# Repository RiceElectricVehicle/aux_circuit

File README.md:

View this project on [CADLAB.io](https://cadlab.io/project/1338). 

# aux_circuit

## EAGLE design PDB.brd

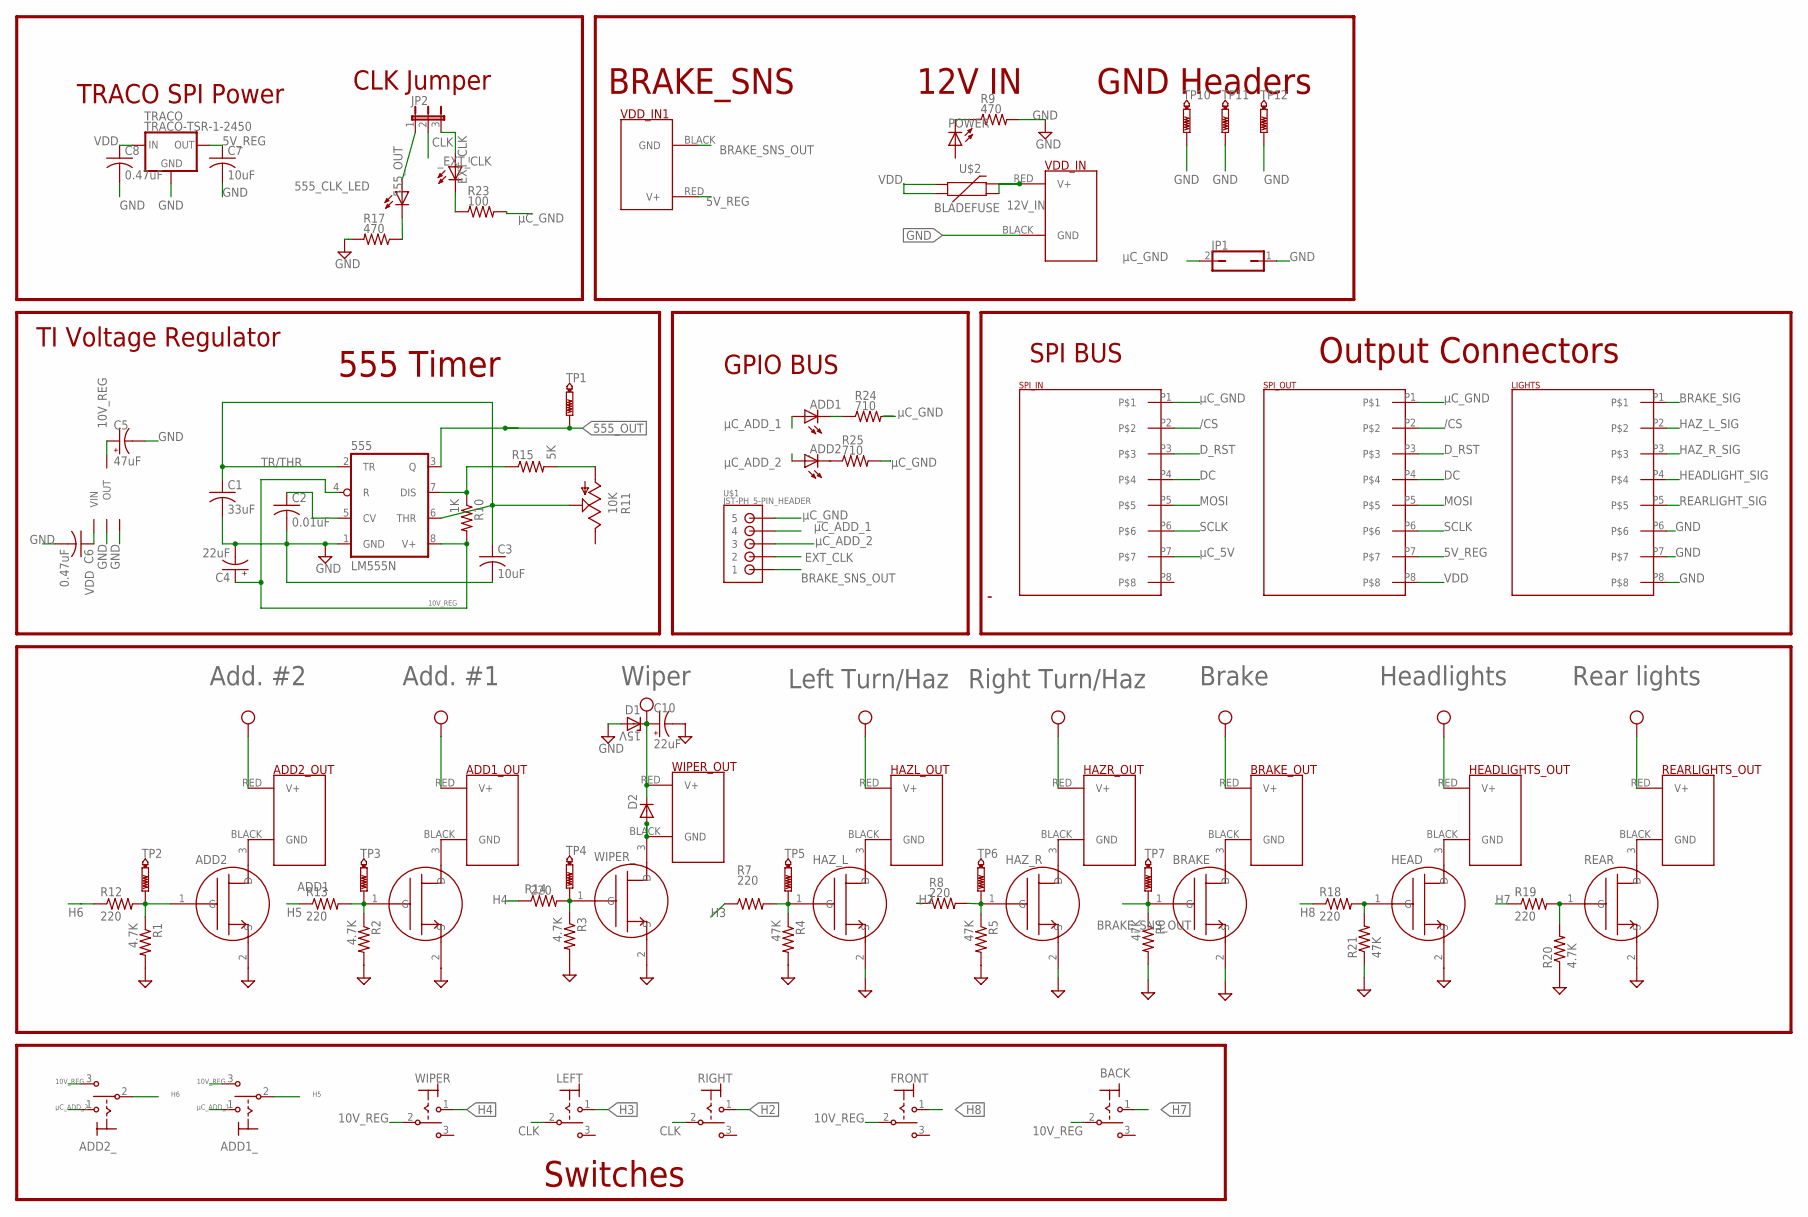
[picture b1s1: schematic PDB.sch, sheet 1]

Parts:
555: LM555N; DIL08
555_CLK_LED: LEDCHIPLED_0805; CHIPLED_0805
ADD1, ADD2: NCV8405ADPAK-3PIN; TO254P1054X240-3
ADD1_, ADD2_: M9040P
ADD1_OUT, ADD2_OUT: POWERPOLE_POWER25A_HORIZONTAL_G2; POWERPOLE_PAIR_25A_HORIZ_G2
BACK: M9040P
BRAKE: NCV8405ADPAK-3PIN; TO254P1054X240-3
BRAKE_OUT: POWERPOLE_POWER25A_HORIZONTAL_G2; POWERPOLE_PAIR_25A_HORIZ_G2
C1: 33uF; C0805
C2: 0.01uF; C0805
C3, C7: 10uF; C0805
C4, C10: 22uF; PANASONIC_C
C5: 47uF; PANASONIC_C
C6, C8: 0.47uF; C0805
D1: 15V; DO41Z10
D2: 1N4446; DO35-10
FRONT: M9040P
HAZL_OUT: POWERPOLE_POWER25A_HORIZONTAL_G2; POWERPOLE_PAIR_25A_HORIZ_G2
HAZR_OUT: POWERPOLE_POWER25A_HORIZONTAL_G2; POWERPOLE_PAIR_25A_HORIZ_G2
HAZ_L: NCV8405ADPAK-3PIN; TO254P1054X240-3
HAZ_R: NCV8405ADPAK-3PIN; TO254P1054X240-3
HEAD: NCV8405ADPAK-3PIN; TO254P1054X240-3
HEADLIGHTS_OUT: POWERPOLE_POWER25A_HORIZONTAL_G2; POWERPOLE_PAIR_25A_HORIZ_G2
JP1: JP1Q; JP1
JP2: JP2E; JP2
LEFT: M9040P
LIGHTS: 8-PIN-MOLEX-RA-FEMALE; 8-PIN-MOLEX
LM2940: LM2940LM; SOT230P700X180-4
POWER: LEDCHIPLED_0805; CHIPLED_0805
R1, R2, R3, R20: 4.7K; R0805
R4, R5, R6, R21: 47K; R0805
R7, R8, R12, R13, R14, R18, R19: 220; R0805
R9, R17: 470; R3225
R10: 1K; R0805
R11: 10K; B25U
R15: 5K; R0805
R23: 100; R0805
R24, R25: 710; R0805
REAR: NCV8405ADPAK-3PIN; TO254P1054X240-3
REARLIGHTS_OUT: POWERPOLE_POWER25A_HORIZONTAL_G2; POWERPOLE_PAIR_25A_HORIZ_G2
RIGHT: M9040P
SPI_IN: 8-PIN-MOLEX-RA-FEMALE; 8-PIN-MOLEX
SPI_OUT: 8-PIN-MOLEX-RA-FEMALE; 8-PIN-MOLEX
TP1, TP2, TP3, TP4, TP5, TP6, TP7: PTR1B2,54; B2,54
TP10, TP11, TP12: PTR1PAD1-13Y; P1-13Y
TRACO: TRACO-TSR-1-2450; SIP3
U$1: JST-PH_5-PIN_HEADER; JST_B5B-PH_HEADER
U$2: BLADEFUSE
VDD_IN, VDD_IN1: POWERPOLE_POWER25A_HORIZONTAL_G2; POWERPOLE_PAIR_25A_HORIZ_G2
WIPER: M9040P
WIPER_: NCV8405ADPAK-3PIN; TO254P1054X240-3
WIPER_OUT: POWERPOLE_POWER25A_HORIZONTAL_G2; POWERPOLE_PAIR_25A_HORIZ_G2
_ADD1, _ADD2: LEDCHIPLED_0805; CHIPLED_0805
_EXT_CLK: LEDCHIPLED_0805; CHIPLED_0805

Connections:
5V_REG: C7.1, SPI_OUT.P7, TRACO.3 (OUT), VDD_IN1.RED (V+)
10V_REG: 555.4 (R), 555.8 (V+), ADD1_.3 (S), ADD2_.3 (S), BACK.2, C4.+, C5.+, FRONT.2, LM2940.3 (OUT), R10.2, WIPER.2
12V_IN: U$2.P$3 (2), U$2.P$4, VDD_IN.RED (V+)
555_OUT: 555.3 (Q), 555_CLK_LED.A, JP2.1, TP1.TP
/CS: SPI_IN.P2, SPI_OUT.P2
BRAKE_SIG: BRAKE.3 (D), BRAKE_OUT.BLACK (GND), LIGHTS.P1
BRAKE_SNS_OUT: BRAKE.1 (G), R6.1, TP7.TP, U$1.P1 (1), VDD_IN1.BLACK (GND)
CLK: JP2.2, LEFT.2, RIGHT.2
CV: 555.5 (CV), C2.1
DC: SPI_IN.P4, SPI_OUT.P4
DIS: 555.7 (DIS), R10.1, R15.1
D_RST: SPI_IN.P3, SPI_OUT.P3
EXT_CLK: JP2.3, U$1.P2 (2), _EXT_CLK.A
GND: 555.1 (GND), ADD1.2 (S), ADD2.2 (S), BRAKE.2 (S), C1.2, C2.2, C3.2, C4.-, C5.-, C6.2, C7.2, C8.2, C10.-, D1.A, HAZ_L.2 (S), HAZ_R.2 (S), HEAD.2 (S), JP1.1, LIGHTS.P6, LIGHTS.P7, LIGHTS.P8, LM2940.2 (GND2), LM2940.4 (GND), R1.2, R2.2, R3.2, R4.2, R5.2, R6.2, R9.2, R17.2, R20.1, R21.1, REAR.2 (S), TP10.TP, TP11.TP, TP12.TP, TRACO.2 (GND), VDD_IN.BLACK (GND), WIPER_.2 (S)
H2: R8.1, RIGHT.1 (O)
H3: LEFT.1 (O), R7.1
H4: R14.1, WIPER.1 (O)
H5: ADD1_.2, R13.1
H6: ADD2_.2, R12.1
H7: BACK.1 (O), R19.1
H8: FRONT.1 (O), R18.1
HAZ_L_SIG: HAZL_OUT.BLACK (GND), HAZ_L.3 (D), LIGHTS.P2
HAZ_R_SIG: HAZR_OUT.BLACK (GND), HAZ_R.3 (D), LIGHTS.P3
HEADLIGHT_SIG: HEAD.3 (D), HEADLIGHTS_OUT.BLACK (GND), LIGHTS.P4
HL_GATE: HAZ_L.1 (G), R4.1, R7.2, TP5.TP
HR_GATE: HAZ_R.1 (G), R5.1, R8.2, TP6.TP
MOSI: SPI_IN.P5, SPI_OUT.P5
unnamed: POWER.C, R9.1
unnamed: 555_CLK_LED.C, R17.1
unnamed: R23.1, _EXT_CLK.C
unnamed: R24.1, _ADD1.C
unnamed: R25.1, _ADD2.C
unnamed: R11.A, R15.2
unnamed: ADD2.1 (G), R1.1, R12.2, TP2.TP
unnamed: ADD2.3 (D), ADD2_OUT.BLACK (GND)
unnamed: HEAD.1 (G), R18.2, R21.2
unnamed: R19.2, R20.2, REAR.1 (G)
unnamed: ADD1.3 (D), ADD1_OUT.BLACK (GND)
unnamed: D2.A, WIPER_.3 (D), WIPER_OUT.BLACK (GND)
unnamed: R3.1, R14.2, TP4.TP, WIPER_.1 (G)
unnamed: ADD1.1 (G), R2.1, R13.2, TP3.TP
REARLIGHT_SIG: LIGHTS.P5, REAR.3 (D), REARLIGHTS_OUT.BLACK (GND)
SCLK: SPI_IN.P6, SPI_OUT.P6
TR/THR: 555.2 (TR), 555.6 (THR), C1.1, C3.1, R11.S
VDD: ADD1_OUT.RED (V+), ADD2_OUT.RED (V+), BRAKE_OUT.RED (V+), C6.1, C8.1, C10.+, D1.C, D2.C, HAZL_OUT.RED (V+), HAZR_OUT.RED (V+), HEADLIGHTS_OUT.RED (V+), LM2940.1 (VIN), REARLIGHTS_OUT.RED (V+), SPI_OUT.P8, TRACO.1 (IN), U$2.P$1 (1), U$2.P$2, WIPER_OUT.RED (V+)
µC_5V: SPI_IN.P7
µC_ADD_1: ADD1_.1 (O), U$1.P4 (4), _ADD1.A
µC_ADD_2: ADD2_.1 (O), U$1.P3 (3), _ADD2.A
µC_GND: JP1.2, R23.2, R24.2, R25.2, SPI_IN.P1, SPI_OUT.P1, U$1.P5 (5)

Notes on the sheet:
555 Timer
12V IN
BRAKE_SNS
Switches
Add. #2
Add. #1
Wiper
Left Turn/Haz
Right Turn/Haz
Brake
Headlights
Rear lights
GND Headers
Output Connectors
GPIO BUS
TRACO SPI Power
TI Voltage Regulator
CLK Jumper
SPI BUS

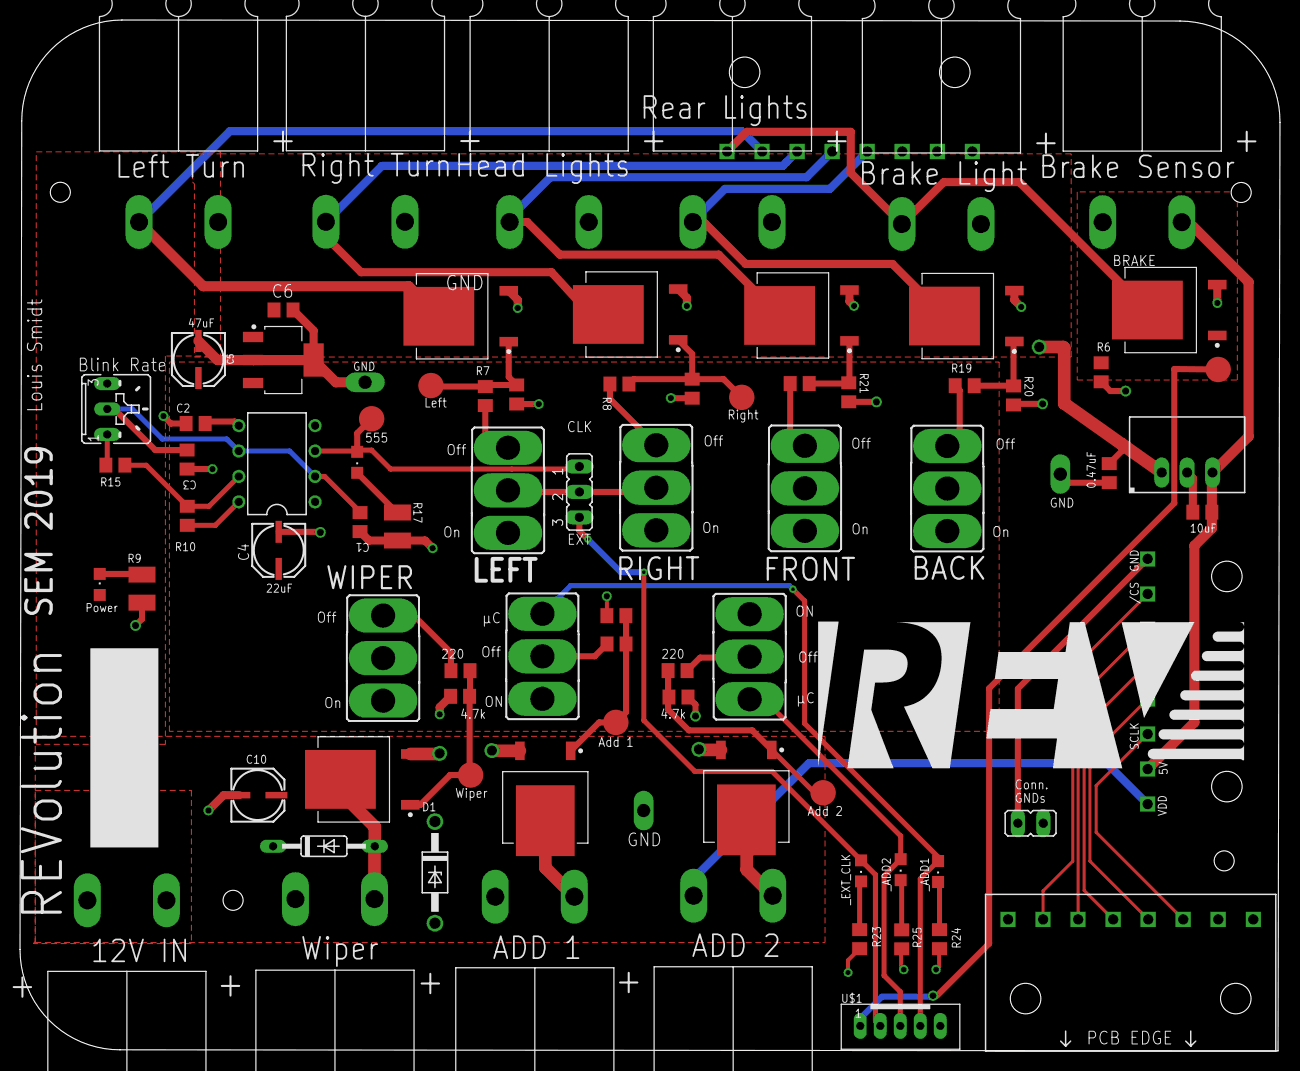
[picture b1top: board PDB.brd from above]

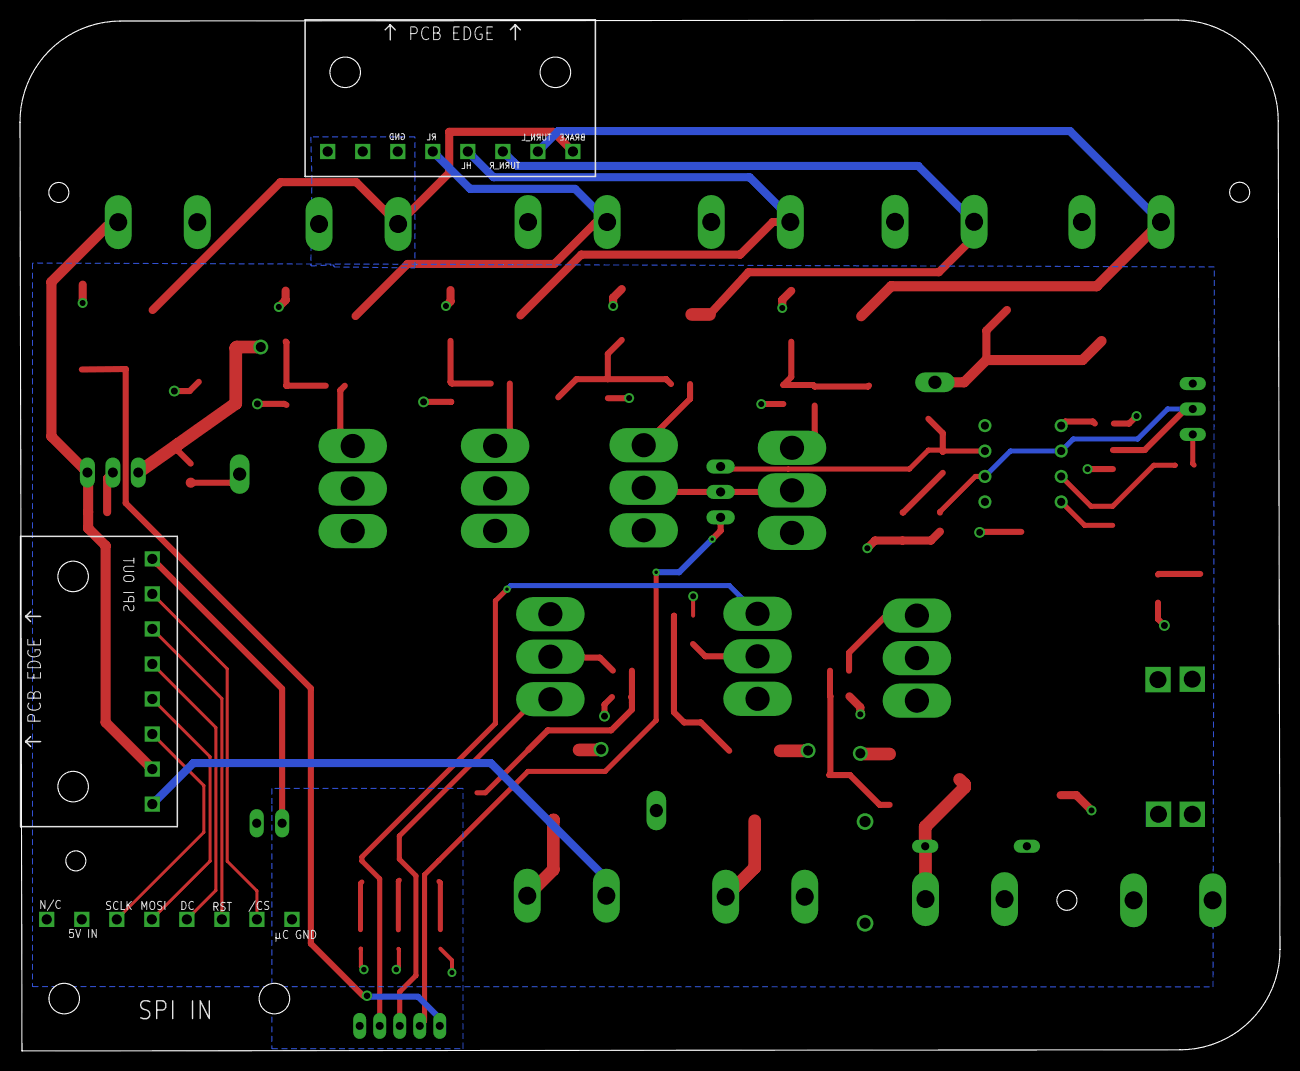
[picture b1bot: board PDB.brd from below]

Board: 2 copper layers, 125.9 x 103.0 mm, 84 parts (2 on the bottom side), 48 nets.

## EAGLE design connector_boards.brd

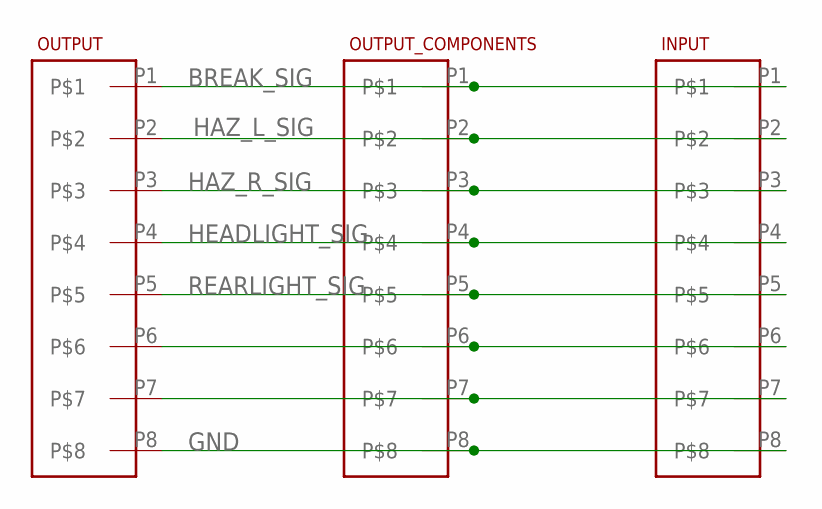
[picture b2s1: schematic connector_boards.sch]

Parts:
INPUT: 8-PIN-MOLEX-RA-FEMALE; 8-PIN-MOLEX
OUTPUT: 8-PIN-MOLEX-RA-FEMALE; 8-PIN-MOLEX
OUTPUT_COMPONENTS: 8-PIN-MOLEX-RA-FEMALE; 8-PIN-MOLEX

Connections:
BREAK_SIG: INPUT.P1, OUTPUT.P1, OUTPUT_COMPONENTS.P1
GND: INPUT.P8, OUTPUT.P8, OUTPUT_COMPONENTS.P8
HAZ_L_SIG: INPUT.P2, OUTPUT.P2, OUTPUT_COMPONENTS.P2
HAZ_R_SIG: INPUT.P3, OUTPUT.P3, OUTPUT_COMPONENTS.P3
HEADLIGHT_SIG: INPUT.P4, OUTPUT.P4, OUTPUT_COMPONENTS.P4
unnamed: INPUT.P6, OUTPUT.P6, OUTPUT_COMPONENTS.P6
unnamed: INPUT.P7, OUTPUT.P7, OUTPUT_COMPONENTS.P7
REARLIGHT_SIG: INPUT.P5, OUTPUT.P5, OUTPUT_COMPONENTS.P5

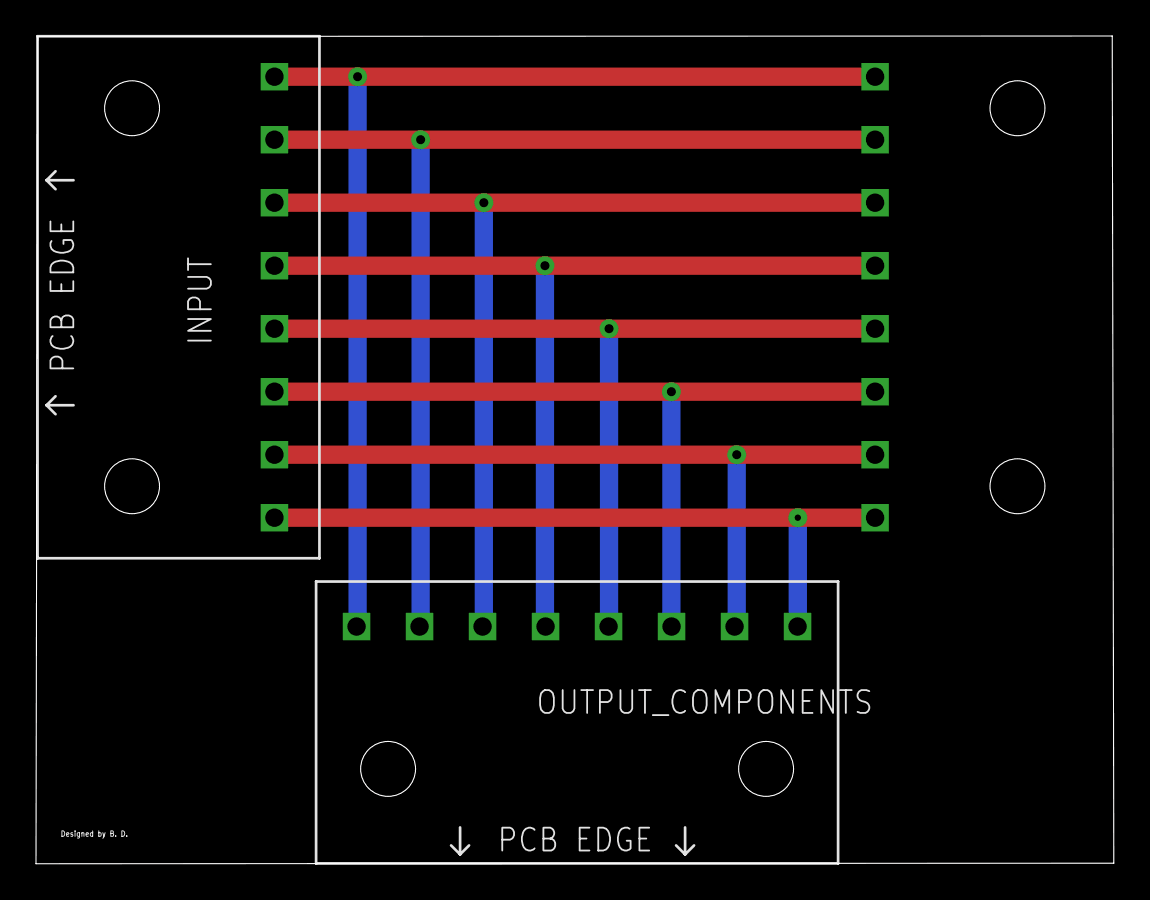
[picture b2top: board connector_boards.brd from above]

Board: 2 copper layers, 59.9 x 46.0 mm, 3 parts (1 on the bottom side), 8 nets.

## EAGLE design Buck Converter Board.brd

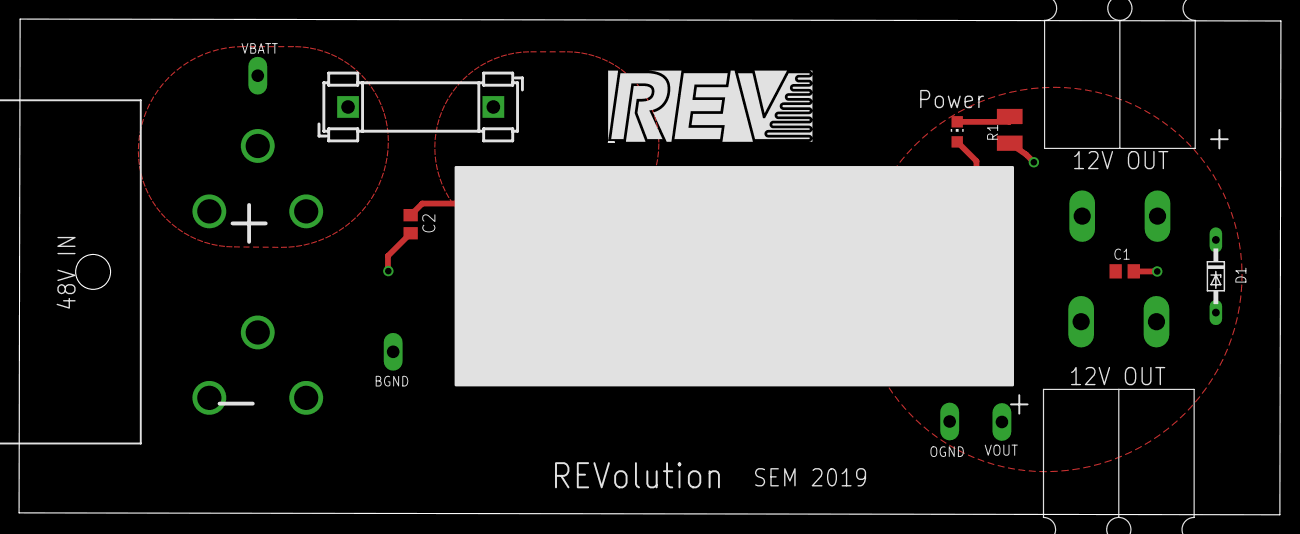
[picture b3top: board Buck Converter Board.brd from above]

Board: 2 copper layers, 132.3 x 52.0 mm, 14 parts (0 on the bottom side), 6 nets.

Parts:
BGND: VBATT; P1-13Y
C1: .47uF; C0805
C2: C0805
D1: 15V; DO34Z7
F1: FUSEBLANK_5X20MM; FUSE_HOLDER_5X20MM
J2, J3: POWERPOLE_POWER25A_HORIZONTAL_G2; POWERPOLE_PAIR_25A_HORIZ_G2
LED1: CHIP-LED0805
OGND: TEST_POINTSPAD1-13Y; P1-13Y
R1: 470; R3225
U$1: BATTERY; SB50POWER_CLAW
UEE150W: UEE150W; DOSA1/8
VBATT: VBATT; P1-13Y
VOUT: TEST_POINTSPAD1-13Y; P1-13Y

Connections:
BGND: BGND.TP, C2.2, U$1.NEG1, U$1.NEG2, U$1.NEG3, UEE150W.ON/OFF, UEE150W.V-
unnamed: LED1.C, R1.2
OGND: C1.2, D1.A, J2.BLACK, J3.BLACK, OGND.TP, R1.1, UEE150W.SNS-, UEE150W.V_OUT-
VBATT: F1.1, U$1.POS1, U$1.POS2, U$1.POS3, VBATT.TP
V_BATT_FUSED: C2.1, F1.2, UEE150W.V+
V_OUT: C1.1, D1.C, J2.RED, J3.RED, LED1.A, UEE150W.SNS+, UEE150W.V_OUT+, VOUT.TP

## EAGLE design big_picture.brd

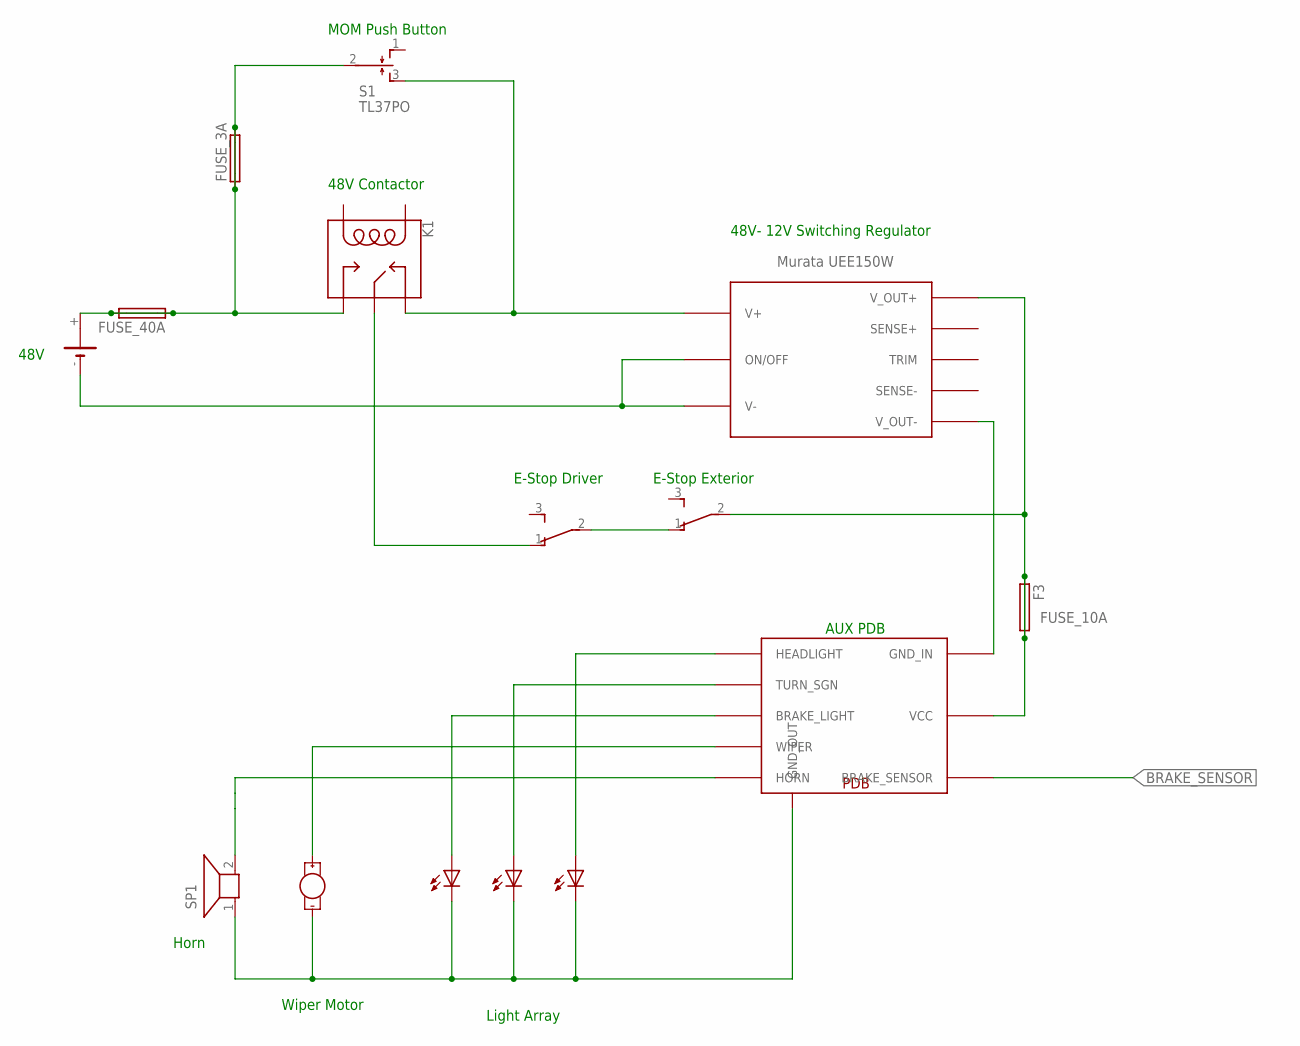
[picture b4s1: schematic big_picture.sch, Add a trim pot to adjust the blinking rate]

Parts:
DZ1: LZR184
E_STOP, E_STOP1: TL36WO; TL3XWO
F3: FUSESH22,5A; SH22,5A
FUSE_3A, FUSE_40A: FUSESH22,5A; SH22,5A
G1: CR1/2
K1: RELAY-SPDT-JZC-11F; RELAY-JZC
M1: MOTOR10MM; VIBE-MOTOR-10MM
S1: TL37PO; TL3XPO
SP1: AL30P

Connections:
FUSE_10A: E_STOP1.2, F3.1, F3.2
unnamed: E_STOP.2, E_STOP1.1 (O)
unnamed: E_STOP.1 (O), K1.4 (MAIN)
unnamed: FUSE_3A.1, FUSE_3A.2, FUSE_40A.1, FUSE_40A.2, G1.+, K1.3 (NO), S1.2
unnamed: K1.2 (NC), S1.3 (S)
PDB_GND: DZ1.K1 (C), DZ1.K2 (C), DZ1.K3 (C), M1.-, SP1.1

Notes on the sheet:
48V- 12V Switching Regulator
E-Stop Driver
E-Stop Exterior
MOM Push Button
Light Array
48V
48V Contactor
AUX PDB
Wiper Motor
Horn

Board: 2 copper layers, 14 parts (0 on the bottom side), 6 nets, no tracks yet.

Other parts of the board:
U$1: AUX
U$2: BUCK
U$3: HORN

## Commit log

2018-09-25 added 555 and switches
2018-09-25 named some wires
2018-10-02 named FET gate input nets
2018-10-03 moved FET around
2018-10-03 finished PDB schematic
2018-10-03 more stuff
2018-10-03 final, i swear
2018-10-03 apparently stuff changed
2018-10-03 created PDB board
2018-10-03 placing components on board
2018-10-03 ratsnest to remove some airwires
2018-10-04 big picture circuit?
2018-10-04 Backlink to CADLAB.io has been added.
2018-10-04 Made a note on trim pot
2018-10-07 updated board layout
2018-10-07 changed stuff
2018-10-07 board layout
2018-10-11 updated big picture
2018-10-11 big picture
2018-10-11 added trim pot
2018-10-11 changed PDB
2018-10-11 created buck converter board
2018-10-11 added custom part for buck
2018-10-11 moved cmoponents on buck converter board around
2018-10-11 redid general schematic
2018-10-11 improved layout of 555 timer
2018-10-11 modified ground plane in PDB
2018-10-12 obviously changed something, right?
2018-10-12 playing around, switched order of switches and FETs
2018-10-12 cuck changes
2018-10-13 removed trim pot and bullshit from buck board
2018-10-14 did initial route of PDB
2018-10-14 more routing
2018-10-14 ratsnest
2018-10-15 continued routing of PDB
2018-10-15 added text to PDB board
2018-10-15 routed buck board
2018-10-15 changed polygons on buck board
2018-10-15 named nets on buck board
2018-10-15 redid polygon for buck board
2018-10-18 Made the text larger on the board for reading
2018-10-18 some notes :100:
2018-10-18 ratsnest. no changes.
2018-10-19 PowerPole Library
2018-10-20 thick traces
2018-10-20 wide traces
2018-10-20 added stuff to pdb
2018-10-21 changed GND of brake sensor to VDD
2018-10-21 thickened traces
2018-10-22 changed switches for Add 1, 2.
    made compatible with JST connector
2018-10-22 changed a lot of routing, near final version with JSTs
2018-10-22 updated PDB board
2018-10-22 Put in MOLEX connector into PDB circuit
2018-10-23 added Molex for MC signals
2018-10-23 Revert "Merge branch 'development' of https://github.com/RiceElectricVehicle/aux_circuit into development"
    This reverts commit 27d2e27f3f052a4aaf18c9661e4c723c8fc48156, reversing
    changes made to 108f46fff09557bc467faa637bceaf60ec43af79.
2018-10-24 realigned molex connectors
2018-10-25 changed
2018-10-26 changed a bunch of stuff
2018-10-28 reroutes Control in and out
2018-10-28 adds clock select jumper
2018-10-29 adds jumper to test brake lights
2018-10-29 redoes ground plane, fixes names of components by centering
2018-10-29 messed around with BitMaP, changes orientation of Molex conn on bottom
2018-11-01 added REV Logo, fixed some hidden airwires
2018-11-01 fixes vdd plane, fixes issues discussed in meeting
2018-11-03 Changed diode package, made a trace larger
2018-11-08 added values
2018-11-08 fix planes, move connectors inwards, add REV logo
2018-11-08 center input connector
2018-11-08 connected sense pins on buck board
2018-11-08 removed dimensions from buck board
2018-11-08 names on buck board
2018-11-08 organized folders. Added connector board
2018-11-11 some changes to buck board
2018-11-11 final updates
2018-11-11 more changes idk
2018-11-12 changed buck board
2018-11-13 changed boards, added LEDs
2018-11-13 LEDs
2018-11-13 changed bypass cap on 555 to 22uF panasonic
2018-11-15 No changes?
2018-11-15 added connector board
2018-11-17 final changes
2018-11-29 ESD built - big lou
2018-11-29 Built ESD
2018-12-02 Latest board added
2018-12-02 Connector board changed, connector problem corrected, changed trace width, drill size and via diammeter
2018-12-02 deleted unecessary revision files
2019-01-27 redid molex pins
2019-02-11 new jumpers, added TRACO 5v, added JST, changed MOELX, added circuit breaker, added voltage regulator for 555
2019-02-11 moved position of circuit breaker
2019-02-11 changed grounds on LEDs to match DGND
2019-02-11 modified PCB layout to reduce ovreall size
2019-02-11 further pcb modifications
2019-02-11 PCB layout changes
2019-02-11 pcb layout
2019-02-11 lots of PCB changes
2019-02-12 pcb layout changes, again
2019-02-12 changed layout of grounds on PCB
2019-02-12 changed a bunch of PCB stuff
2019-02-12 close to final pcb layout, not yet routed
2019-02-14 board planes layout
2019-02-14 close to final pcb layout
2019-02-26 updated molex sizes on connector board, finished PDB
2019-02-26 more updates to pdb
2019-02-26 added text to pdb
2019-02-26 added caps to in/out of voltage converters
2019-02-26 rmoved extraneous traces, ran DRC
2019-03-20 some changes, hope this doesnt break anything
2019-03-23 some changes

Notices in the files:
parts and their libraries:
SparkFun-Capacitors: Licensing: Creative Commons ShareAlike 4.0 International - https://creativecommons.org/licenses/by-sa/4.0
